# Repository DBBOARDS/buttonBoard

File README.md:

# buttonBoard
These are the Eagle files for the Button Board.

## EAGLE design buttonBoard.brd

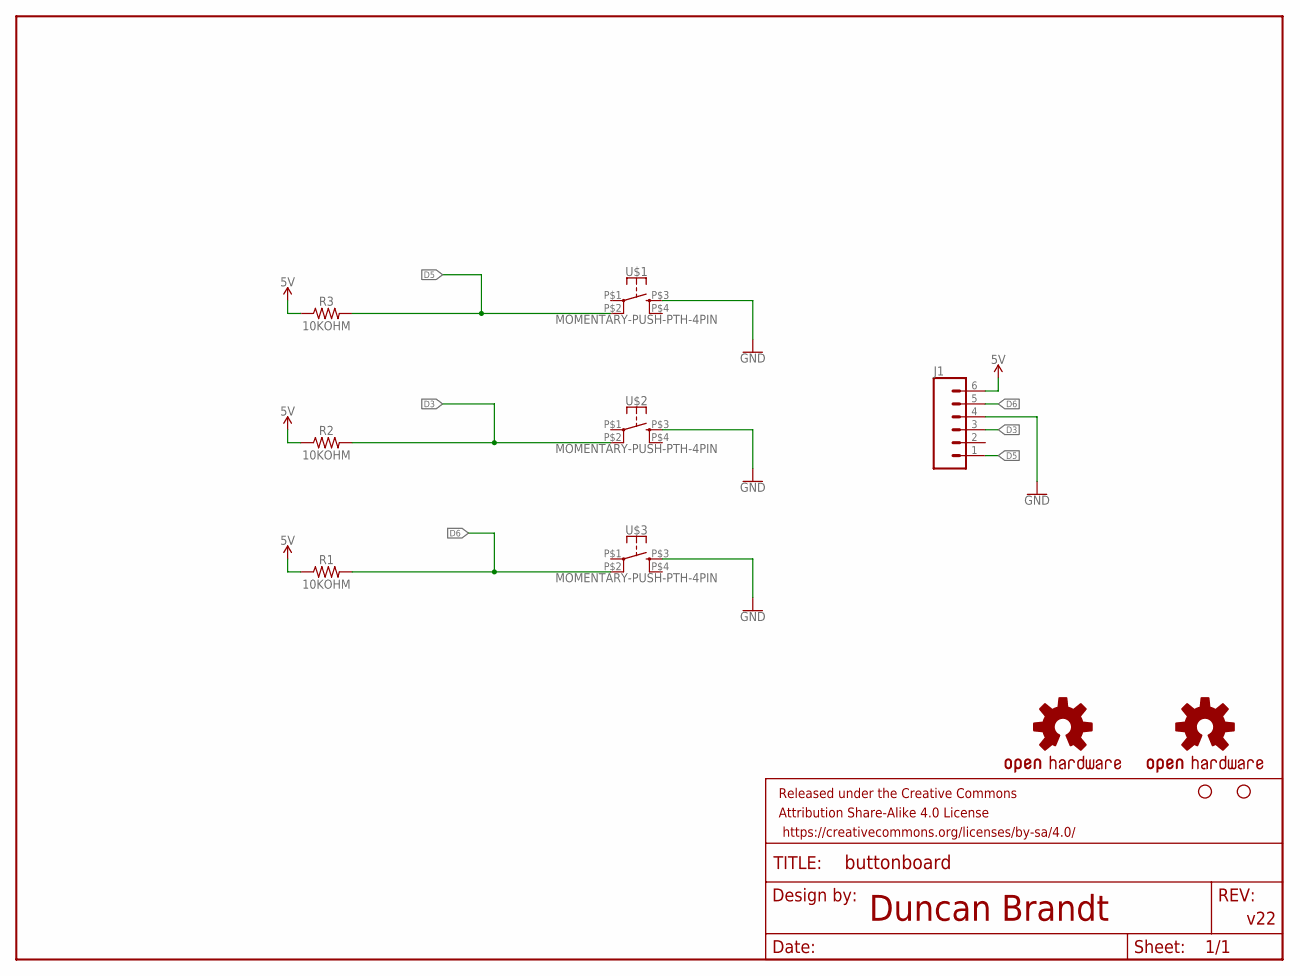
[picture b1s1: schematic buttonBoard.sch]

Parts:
FRAME2: FRAME-LETTER; CREATIVE_COMMONS
J1: CONN_06SILK_FEMALE_PTH; 1X06
JP3, JP6: STAND-OFF
R1, R2, R3: 10KOHM; AXIAL-0.3
U$1, U$2, U$3: MOMENTARY-PUSH-PTH-4PIN; SOFTPUSH_BTN_PTH_0.2INCH
U$4, U$16: OSHW-LOGOS; OSHW-LOGO-S

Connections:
5V: J1.6, R1.P$1 (1), R2.P$1 (1), R3.P$1 (1)
D3: J1.3, R2.P$2 (2), U$2.P$2 (2)
D5: J1.1, R3.P$2 (2), U$1.P$2 (2)
D6: J1.5, R1.P$2 (2), U$3.P$2 (2)
GND: J1.4, U$1.P$3 (3), U$2.P$3 (3), U$3.P$3 (3)

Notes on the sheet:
Duncan Brandt
v22

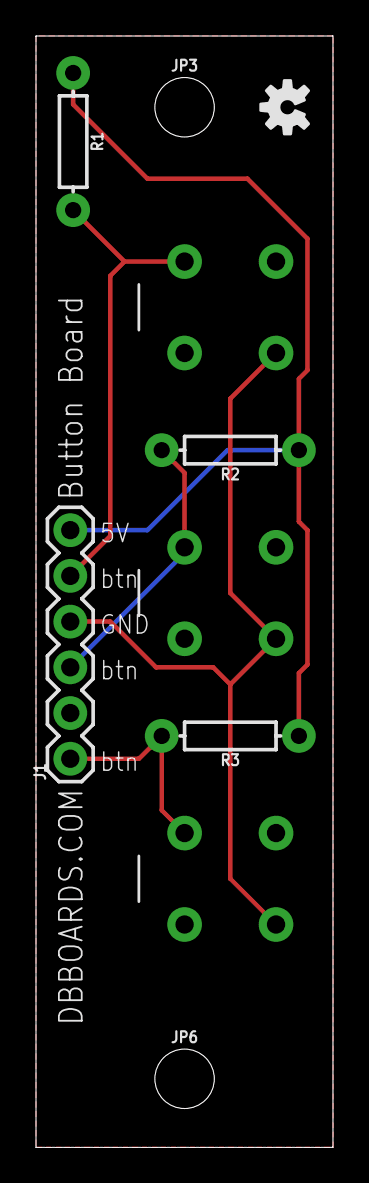
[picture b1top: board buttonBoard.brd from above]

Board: 2 copper layers, 16.5 x 61.7 mm, 12 parts (1 on the bottom side), 5 nets.

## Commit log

2018-02-13 eagle files

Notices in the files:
parts and their libraries:
DB-SYMBOLS: Licensing: Creative Commons ShareAlike 4.0 International - https://creativecommons.org/licenses/by-sa/4.0
DB-SYMBOLS: Released under the Creative Commons Attribution Share-Alike 4.0 License
DB-SYMBOLS: https://creativecommons.org/licenses/by-sa/4.0
